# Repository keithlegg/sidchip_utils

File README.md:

# sidchip_utils

If you ever get the chance to purchase 30 rusty old SID chips from an engineer who worked at Commodore .... 

DONT DO IT! Put your energy into something else.  

This a small collection of tools, references files, and errata making those old chips sing.

What it is:

siduino           - Kicad project / Gerbers 
                    A one off PCB design thats an arduino (atmega328p) that has a SID chip on it 
                    technically you could program it with the arduino tools if you mapped the pins out properly, but I havent tried it has a 12V and 5V power bus to satisfy the analog-y power needs of the old chips. They run hot. 

siduino firmwware - AVR firmware to issue commands to the SID chip from an AtMega328. 
                    There is some experimental assembly language driver and some experimental midi in/out.  

sidcom            - unfinished. A aerial protocol to talk to the SID chip from a modern machine. The board is flawed, the TX/RX
                    pins on the AVR share the lower two bits of the SID chip data bus, so a new board is needed before this can be used. A prototype board is under development. 

python tools      - Havent done anything yet. The RX/TX flaw really makes this board suck. I need to build a better one 
                    with a bigger chip and two SIDs for stereo. maybe someday. 

If you are crazy enough to want to build one yourself (beware this revision has the TX/RX flaw): 

https://oshpark.com/profiles/klegg

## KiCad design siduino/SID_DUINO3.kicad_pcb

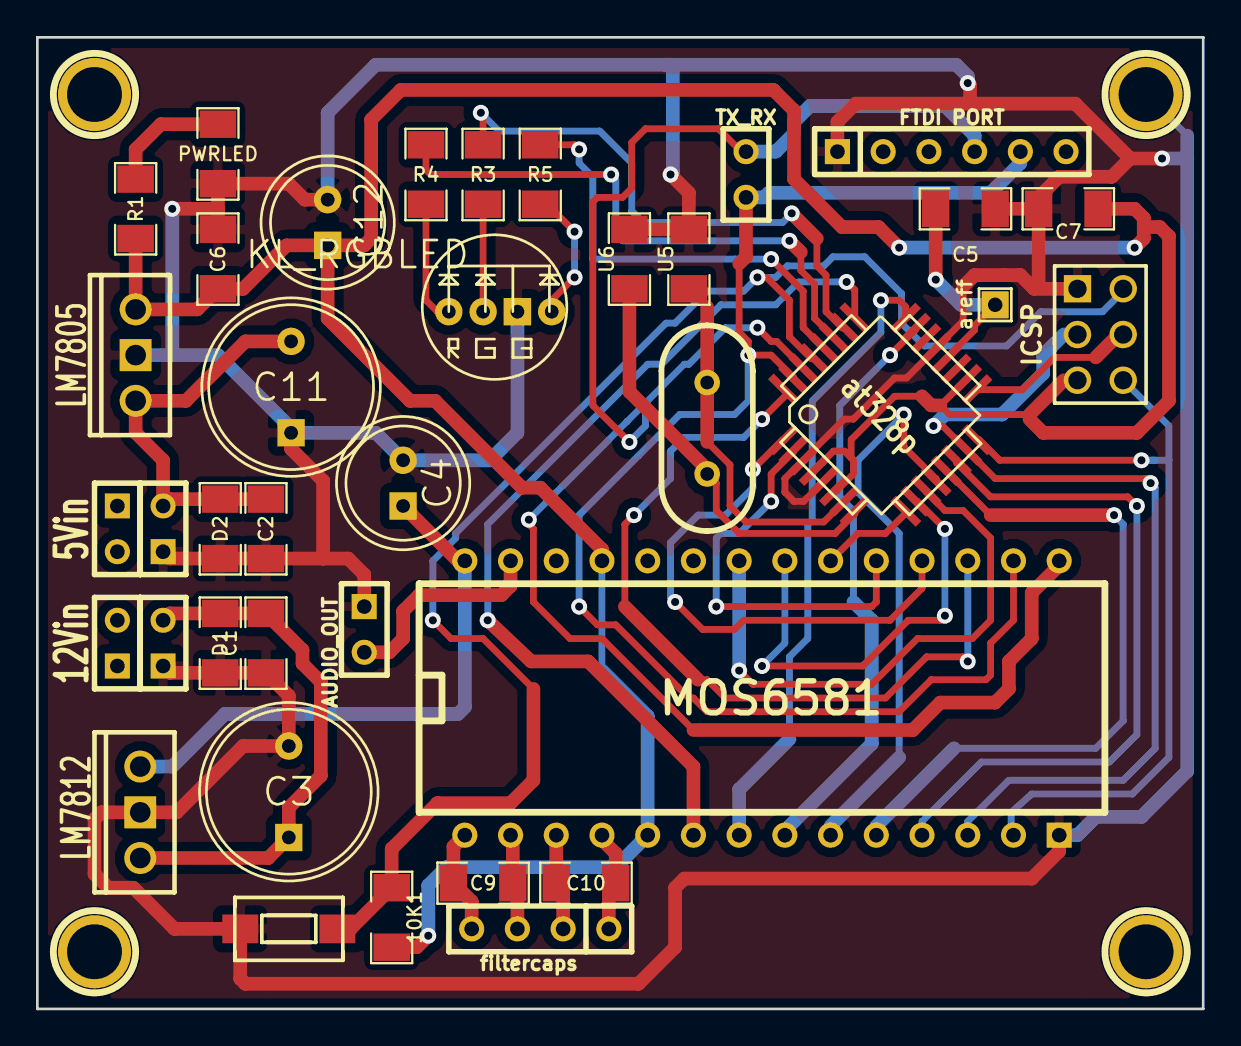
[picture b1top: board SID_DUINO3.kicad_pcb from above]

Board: 2 copper layers, 64.8 x 54.0 mm, 30 parts (0 on the bottom side), 21 nets.

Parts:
5Vin: 5V_IN; SIL-2
10K1: R; SM1206
12Vin: 12V_IN; SIL-2
AUDIO_OUT: AudioOut; SIL-2
C1, C2, C5, C9, C10: C; SM1206
C3, C11: KL_330uf
C4, C12: KL_100uf
C6: .1uf; SM1206
C7: 4.7uf; SM1206
D1, D2: DIODE; SM1206
FTDI PORT: FTDI; SIL-6
ICSP: ICSP; pin_array_3x2
PWRLED: LED; SM1206
R1, R3, R4, R5: R; SM1206
TX_RX: UART; SIL-2
U5, U6: 18pf; SM1206
areff: CONN_1; SIL-1
at328p: TQFP32
filtercaps: Val**; SIL-4

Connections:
/5V: 10K1.2, C6.2, C7.1, C12.1, ICSP.2, R1.1, at328p.4, at328p.6, at328p.18
/5vin: 5Vin.2, C2.1, C11.1, D2.2
/12vin: 12Vin.2, C1.1, C3.1, D1.2
/A3: R3.1, at328p.26
/A4: R4.1, at328p.27
/A5: R5.1, at328p.28
/D11: ICSP.4, at328p.15
/D12: ICSP.1, at328p.16
/D13: ICSP.3, at328p.17
/RST: 10K1.1, ICSP.5, at328p.29
/RX_D1: FTDI PORT.5, TX_RX.1, at328p.31
/TX_D0: FTDI PORT.4, TX_RX.2, at328p.30
GND: 5Vin.1, 12Vin.1, AUDIO_OUT.1, C1.2, C2.2, C3.2, C4.2, C5.2, C6.1, C7.2, C11.2, C12.2, D1.1, D2.1, FTDI PORT.1, ICSP.6, PWRLED.2, U5.2, U6.2, at328p.3, at328p.5, at328p.21
unnamed: C5.1, areff.1, at328p.20
unnamed: PWRLED.1, R1.2
unnamed: C10.1, filtercaps.1
unnamed: C9.1, filtercaps.3
unnamed: C10.2, filtercaps.2
unnamed: C9.2, filtercaps.4
unnamed: U5.1, at328p.7
unnamed: U6.1, at328p.8

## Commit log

2021-01-21 first
2021-01-21 second
2021-01-28 image
2021-01-28 blah
2021-01-28 test
2021-02-07 it makes sound!
2021-02-07 added poke() command to match C64 registers
2021-02-08 it works!
2021-02-08 tested all three voices!
2021-02-08 working awesome!
2021-02-11 asm experiment
2021-02-12 midi transmit test --- works!
2021-02-12 silly song in midi
2021-02-13 added midi in/out
2021-02-14 midi receive data!
2021-02-16 use interrupt on clock pin as audio out test
2021-02-16 added ring mod, sync demos
